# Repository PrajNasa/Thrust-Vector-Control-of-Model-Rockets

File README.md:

# Thrust-Vector-Control-of-Model-Rockets
Arduino based Flight Computer for Implementing Thrust Vector Control of Model Rockets

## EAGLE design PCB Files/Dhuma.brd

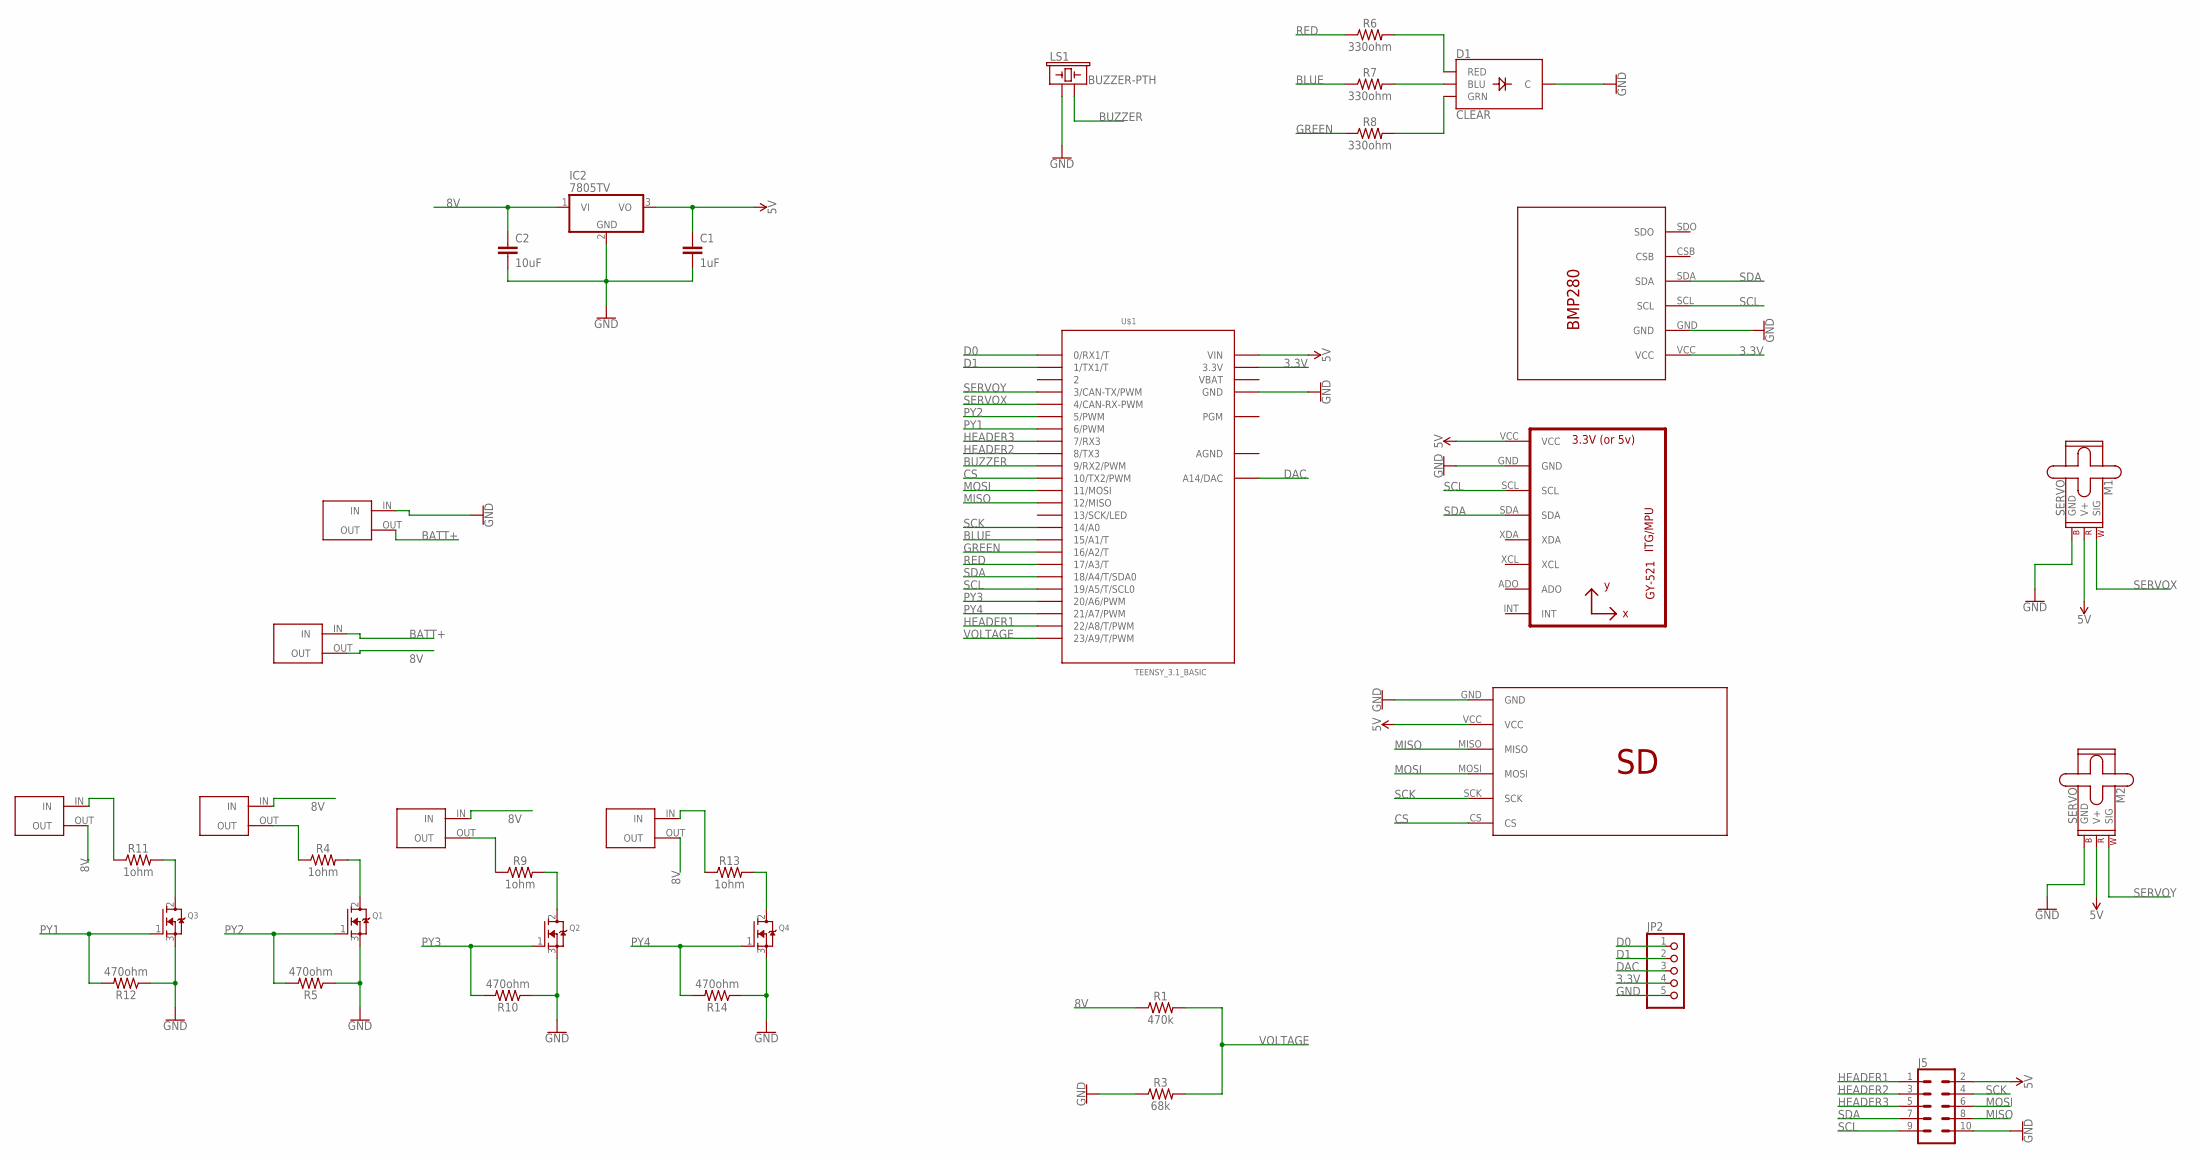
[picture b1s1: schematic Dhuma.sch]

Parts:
C1: 1uF; CAP-PTH-2.54
C2: 10uF; CAP-PTH-2.54
D1: CLEAR; LED-RGB-THRU
IC2: 7805TV; TO220V
J5: CONN_05X2NO_SILK; 2X5_NOSILK
JP2: PINHD-1X5; 1X05
LS1: BUZZER-PTH; BUZZER-12MM
M1, M2: SERVO; 1X03
Q1, Q2, Q3, Q4: MOSFET-NGDS_TO220V; TO220V
R1: 470k; AXIAL-0.3
R3: 68k; AXIAL-0.3
R4, R9, R11, R13: 1ohm; AXIAL-0.3
R5, R10, R12, R14: 470ohm; AXIAL-0.3
R6, R7, R8: 330ohm; AXIAL-0.3
U1: GY-521MPU6050; GY-521
U$1: TEENSY_3.1_BASIC
U$2: BMP280
U$3: SDCARD
U$4, U$5, U$6, U$7, U$8, U$9: TERMINALBLOCKUP

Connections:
3.3V: JP2.4, U$1.3.3V, U$1.3.3V1 (3.3V), U$2.VCC
5V: C1.1, IC2.3 (VO), J5.2, M1.2 (V+), M2.2 (V+), U1.VCC, U$1.VIN, U$3.VCC
8V: C2.1, IC2.1 (VI), R1.P$1 (1), U$4.IN, U$5.OUT, U$6.IN, U$7.OUT, U$9.OUT
AGND: U$1.AGND
BATT+: U$8.OUT, U$9.IN
BLUE: R7.P$1 (1), U$1.15/A1 (15/A1/T)
BUZZER: LS1.- (2), U$1.9 (9/RX2/PWM)
CS: U$1.10 (10/TX2/PWM), U$3.CS
D0: JP2.1, U$1.0 (0/RX1/T)
D1: JP2.2, U$1.1 (1/TX1/T)
DAC: JP2.3, U$1.A14 (A14/DAC)
GND: C1.2, C2.2, D1.2 (C), IC2.2 (GND), J5.10, JP2.5, LS1.+ (1), M1.3 (GND), M2.3 (GND), Q1.3 (S), Q2.3 (S), Q3.3 (S), Q4.3 (S), R3.P$1 (1), R5.P$1 (1), R10.P$1 (1), R12.P$1 (1), R14.P$1 (1), U1.GND, U$1.GND, U$1.GND1 (GND), U$2.GND, U$3.GND, U$8.IN
GREEN: R8.P$1 (1), U$1.16/A2 (16/A2/T)
HEADER1: J5.1, U$1.22/A8 (22/A8/T/PWM)
HEADER2: J5.3, U$1.8 (8/TX3)
HEADER3: J5.5, U$1.7 (7/RX3)
MISO: J5.8, U$1.12 (12/MISO), U$3.MISO
MOSI: J5.6, U$1.11 (11/MOSI), U$3.MOSI
unnamed: D1.1 (RED), R6.P$2 (2)
unnamed: D1.3 (GRN), R8.P$2 (2)
unnamed: D1.4 (BLU), R7.P$2 (2)
unnamed: Q1.2 (D), R4.P$2 (2)
unnamed: R11.P$1 (1), U$5.IN
unnamed: R4.P$1 (1), U$4.OUT
unnamed: Q2.2 (D), R9.P$2 (2)
unnamed: R13.P$1 (1), U$7.IN
unnamed: R9.P$1 (1), U$6.OUT
unnamed: Q3.2 (D), R11.P$2 (2)
unnamed: Q4.2 (D), R13.P$2 (2)
PY1: Q3.1 (G), R12.P$2 (2), U$1.6 (6/PWM)
PY2: Q1.1 (G), R5.P$2 (2), U$1.5 (5/PWM)
PY3: Q2.1 (G), R10.P$2 (2), U$1.20/A6 (20/A6/PWM)
PY4: Q4.1 (G), R14.P$2 (2), U$1.21/A7 (21/A7/PWM)
RED: R6.P$1 (1), U$1.17/A3 (17/A3/T)
SCK: J5.4, U$1.14/A0, U$3.SCK
SCL: J5.9, U1.SCL, U$1.19/A5 (19/A5/T/SCL0), U$2.SCL
SDA: J5.7, U1.SDA, U$1.18/A4 (18/A4/T/SDA0), U$2.SDA
SERVOX: M1.1 (SIG), U$1.4 (4/CAN-RX-PWM)
SERVOY: M2.1 (SIG), U$1.3 (3/CAN-TX/PWM)
VBAT: U$1.VBAT
VOLTAGE: R1.P$2 (2), R3.P$2 (2), U$1.23/A9 (23/A9/T/PWM)

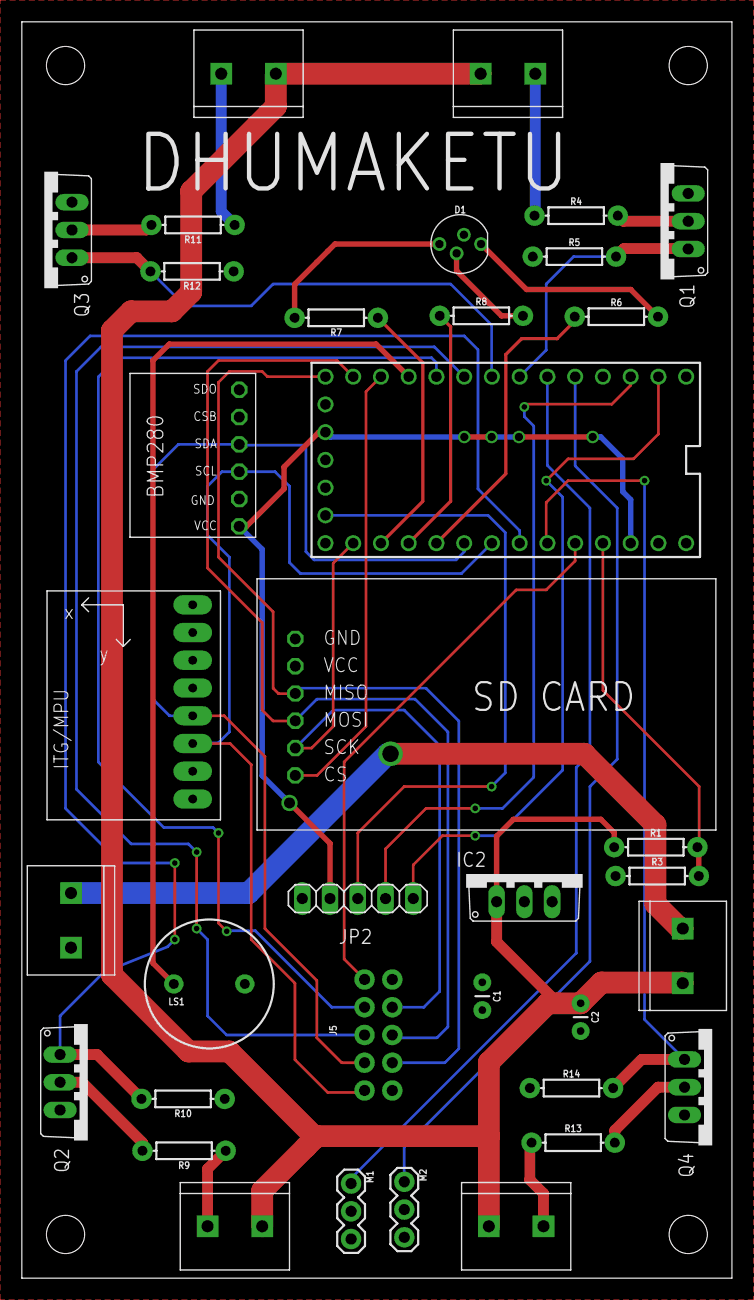
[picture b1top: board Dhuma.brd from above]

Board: 2 copper layers, 65.0 x 115.0 mm, 36 parts (0 on the bottom side), 39 nets.

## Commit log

2020-05-10 Create PCB Files
2020-05-10 Create forever

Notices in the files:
parts and their libraries:
SparkFun-Capacitors: Licensing: Creative Commons ShareAlike 4.0 International - https://creativecommons.org/licenses/by-sa/4.0
